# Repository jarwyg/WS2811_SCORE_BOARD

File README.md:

# WS2811_SCORE_BOARD

W 2017 wraz z znajomym z roku stworzyliśmy tablicę wyników zbudowaną z wykorzystaniem pasków LED WS2811.

W 2024 projekt został ulepszony pod względem hardware oraz firmware. Aktualnie jest opublikownay jako open-source (MIT License) 

# Firmware

Firmware jest napisany w jęzku c.
Projekt był stworzony w Eclipse z AVR plugin (kompilator avr-gcc). Katalog Release zawiera pliki makefile więc można projekt skompliować z poziomu terminala.
Gotowe pliki binarne można znaleźć poniżej

[Firmware Release v1.2](https://github.com/jarwyg/WS2811_SCORE_BOARD/releases/tag/v1.2)

# Receiver

Odbiornik działa na mikrokontrolerze Atmega88/168/328 (16MHz - zawnętrzny oscylator).
Czas jest brany z RTC PCF8563.
Płytka powinna mieć wgrany bootloader z arduino UNO. Dzięki temu po podłączeniu przejściówki USB-UART łatwiej będzie wgrać aktualizację/zobaczyć debug podczas pracy układu. Tablica prawdopodobnie będzie w niedostępnym miejscu więc zalecam zostawienie długiego przewodu USB/RS232 

PCB

# Transmitter

Pilot działa na mikrokontrolerze Atmega88/168/328 (8MHz - wewnętrzny oscylator)
Domyślnie jest w trybie uśpienia i pownien pobierać mniej niż 70uA.
Komunikacja z odbiornikiem odbywa się tylko w jedną stronę.

Opis przycisków

PCB

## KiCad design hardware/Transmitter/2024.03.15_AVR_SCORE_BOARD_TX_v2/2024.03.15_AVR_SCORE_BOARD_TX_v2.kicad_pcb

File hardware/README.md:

# WS2811_SCORE_BOARD
F_CPU 8MHz - Internal oscillator

External oscillator not required

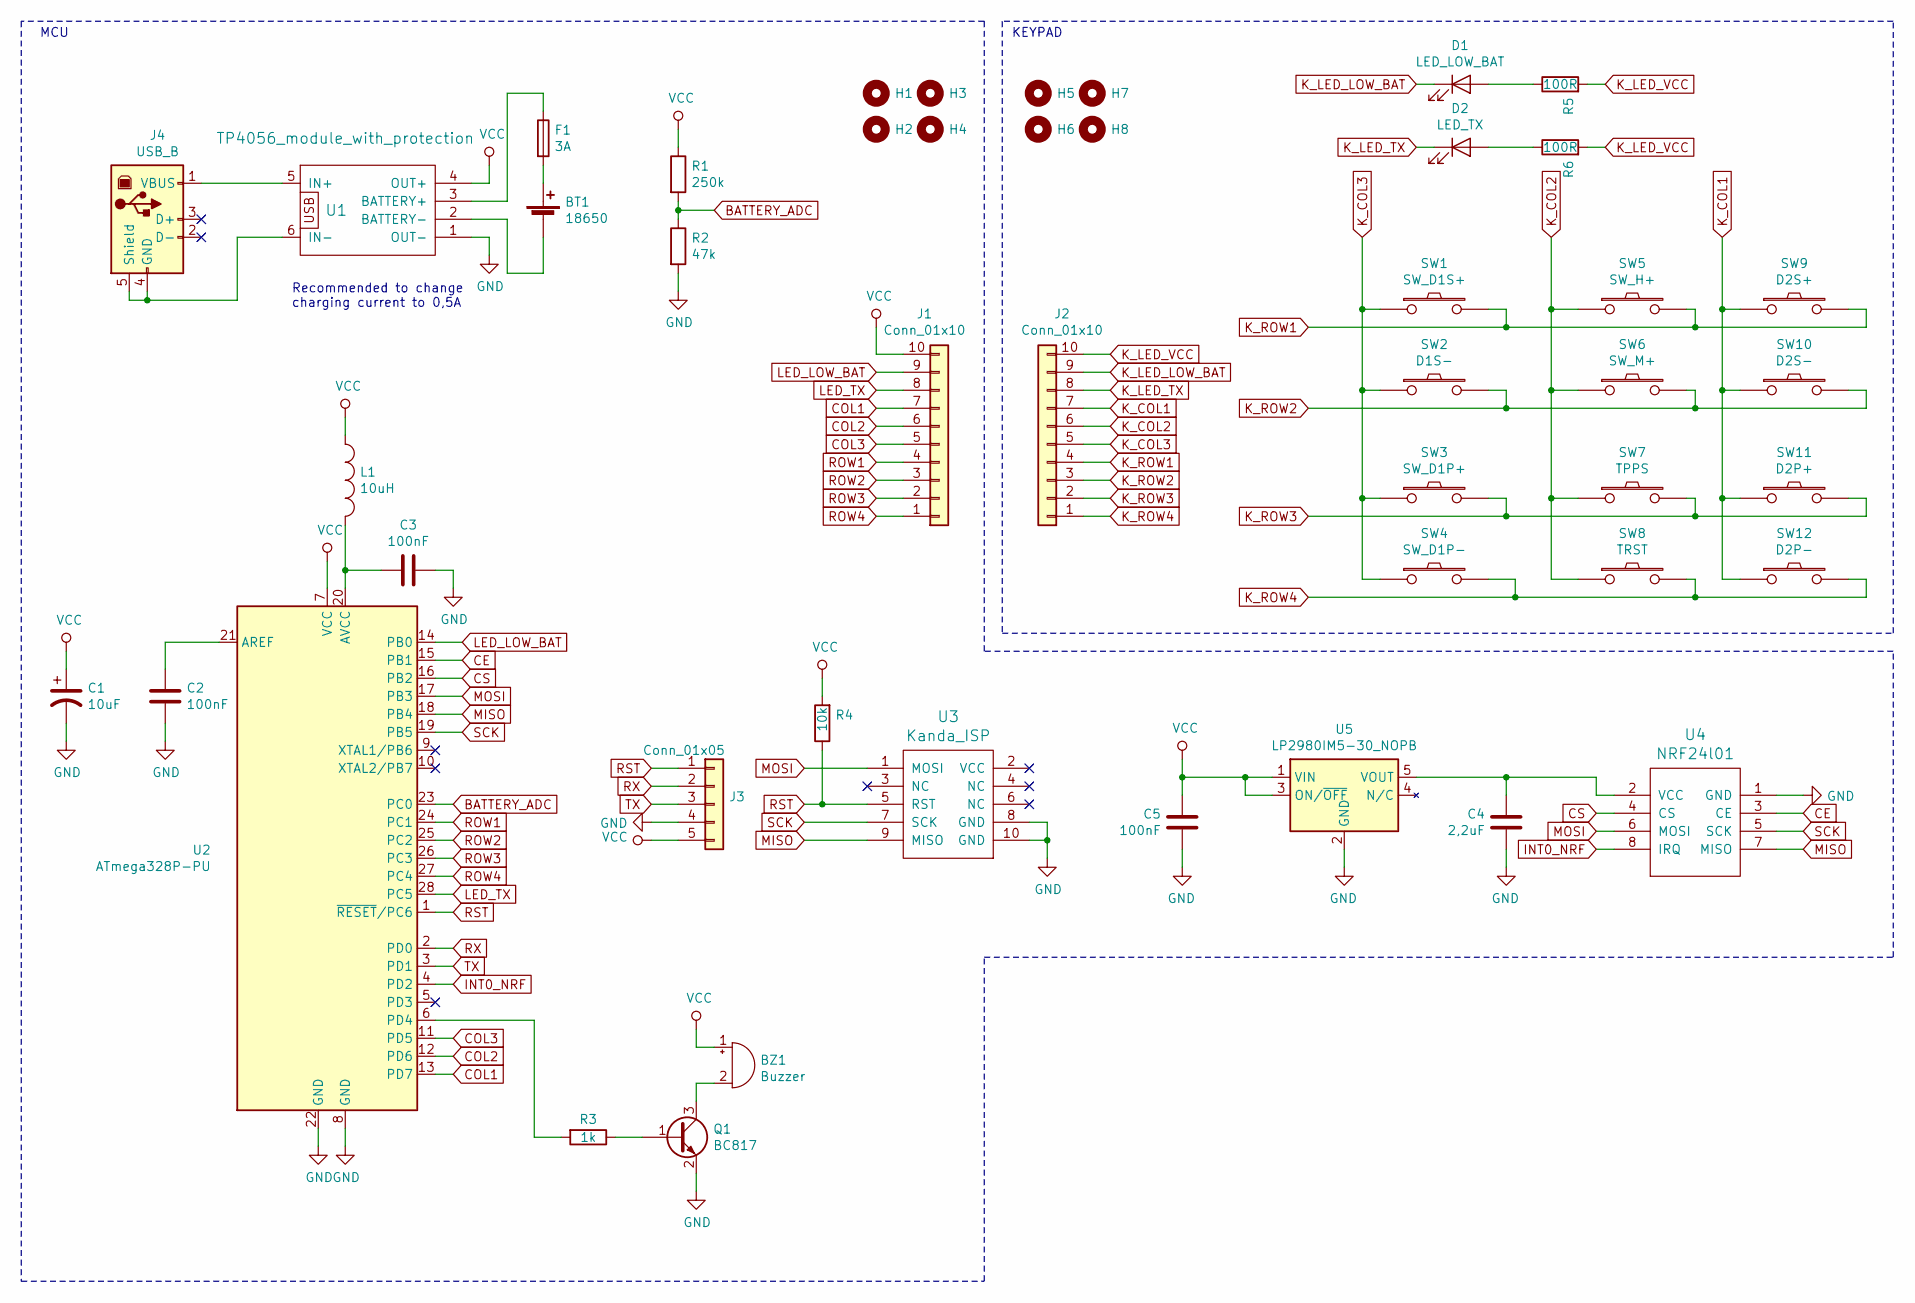
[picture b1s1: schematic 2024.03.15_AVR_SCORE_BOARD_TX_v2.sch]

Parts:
BT1: 18650; BatteryHolder_MPD_BH-18650-PC2
BZ1: Buzzer; BUZZER(7,5mm)
C1: 10uF; C(2,5mm)
C2, C3, C5: 100nF; C_0805_2012Metric_Pad1.15x1.40mm_HandSolder
C4: 2,2uF; C_0805_2012Metric_Pad1.15x1.40mm_HandSolder
D1: LED_LOW_BAT; LED_D3.0mm
D2: LED_TX; LED_D3.0mm
F1: 3A; Fuse_0805_2012Metric_Pad1.15x1.40mm_HandSolder
H1, H2, H3, H4, H5, H6, H7, H8: MountingHole; MountingHole_3mm
J1, J2: Conn_01x10; conn_10
J3: Conn_01x05; conn_5
J4: USB_B
L1: 10uH; L_0805_2012Metric_Pad1.15x1.40mm_HandSolder
Q1: BC817; SOT-23
R1: 250k; R_MY_DIN0204_L3.6mm_D1.6mm_P7.62mm
R2: 47k; R_MY_DIN0204_L3.6mm_D1.6mm_P7.62mm
R3: 1k; R_MY_DIN0204_L3.6mm_D1.6mm_P7.62mm
R4: 10k; R_0805_2012Metric_Pad1.15x1.40mm_HandSolder
R5, R6: 100R; C_0805_2012Metric_Pad1.15x1.40mm_HandSolder
SW1: SW_D1S+; SW_SMALL(12X12)
SW2: D1S-; SW_SMALL(12X12)
SW3: SW_D1P+; SW_SMALL(12X12)
SW4: SW_D1P-; SW_SMALL(12X12)
SW5: SW_H+; SW_SMALL(6X6)
SW6: SW_M+; SW_SMALL(6X6)
SW7: TPPS; SW_SMALL(12X12)
SW8: TRST; SW_SMALL(12X12)
SW9: D2S+; SW_SMALL(12X12)
SW10: D2S-; SW_SMALL(12X12)
SW11: D2P+; SW_SMALL(12X12)
SW12: D2P-; SW_SMALL(12X12)
U1: TP4056_module_with_protection; TP4056-18650
U2: ATmega328P-PU; DIP-28_W7.62mm
U3: Kanda_ISP; KANDA_ISP
U4: NRF24l01
U5: LP2980IM5-30_NOPB; SOT-23-5

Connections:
BATTERY_ADC: R1.2, R2.1, U2.23 (PC0)
CE: U2.15 (PB1), U4.3 (CE)
COL1: J1.7, U2.13 (PD7)
COL2: J1.6, U2.12 (PD6)
COL3: J1.5, U2.11 (PD5)
CS: U2.16 (PB2), U4.4 (CS)
GND: C1.2, C2.2, C3.1, C4.2, C5.2, J3.4, Q1.2 (E), R2.2, U1.1 (OUT-), U2.8 (GND), U2.22 (GND), U3.8 (GND), U3.10 (GND), U4.1 (GND), U5.2 (GND)
INT0_NRF: U2.4 (PD2), U4.8 (IRQ)
K_COL1: J2.7, SW9.1, SW10.1, SW11.1, SW12.1
K_COL2: J2.6, SW5.1, SW6.1, SW7.1, SW8.1
K_COL3: J2.5, SW1.1, SW2.1, SW3.1, SW4.1
K_LED_LOW_BAT: D1.1 (K), J2.9
K_LED_TX: D2.1 (K), J2.8
K_LED_VCC: J2.10, R5.2, R6.2
K_ROW1: J2.4, SW1.2, SW5.2, SW9.2
K_ROW2: J2.3, SW2.2, SW6.2, SW10.2
K_ROW3: J2.2, SW3.2, SW7.2, SW11.2
K_ROW4: J2.1, SW4.2, SW8.2, SW12.2
LED_LOW_BAT: J1.9, U2.14 (PB0)
LED_TX: J1.8, U2.28 (PC5)
MISO: U2.18 (PB4), U3.9 (MISO), U4.7 (MISO)
MOSI: U2.17 (PB3), U3.1 (MOSI), U4.6 (MOSI)
unnamed: BT1.1 (+), F1.2
unnamed: BT1.2 (-), U1.2 (BATTERY-)
unnamed: BZ1.2 (+), Q1.3 (C)
unnamed: C2.1, U2.21 (AREF)
unnamed: C3.2, L1.2, U2.20 (AVCC)
unnamed: C4.1, U4.2 (VCC), U5.5 (VOUT)
unnamed: D1.2 (A), R5.1
unnamed: D2.2 (A), R6.1
unnamed: F1.1, U1.3 (BATTERY+)
unnamed: J4.1 (VBUS), U1.5 (IN+)
unnamed: J4.4 (GND), J4.5 (Shield), U1.6 (IN-)
unnamed: Q1.1 (B), R3.1
unnamed: R3.2, U2.6 (PD4)
ROW1: J1.4, U2.24 (PC1)
ROW2: J1.3, U2.25 (PC2)
ROW3: J1.2, U2.26 (PC3)
ROW4: J1.1, U2.27 (PC4)
RST: J3.1, R4.1, U2.1 (~RESET~/PC6), U3.5 (RST)
RX: J3.2, U2.2 (PD0)
SCK: U2.19 (PB5), U3.7 (SCK), U4.5 (SCK)
TX: J3.3, U2.3 (PD1)
VCC: BZ1.1 (-), C1.1, C5.1, J1.10, J3.5, L1.1, R1.1, R4.2, U1.4 (OUT+), U2.7 (VCC), U5.1 (VIN), U5.3 (ON/~OFF)

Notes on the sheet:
Recommended to change charging current to 0,5A
KEYPAD
MCU

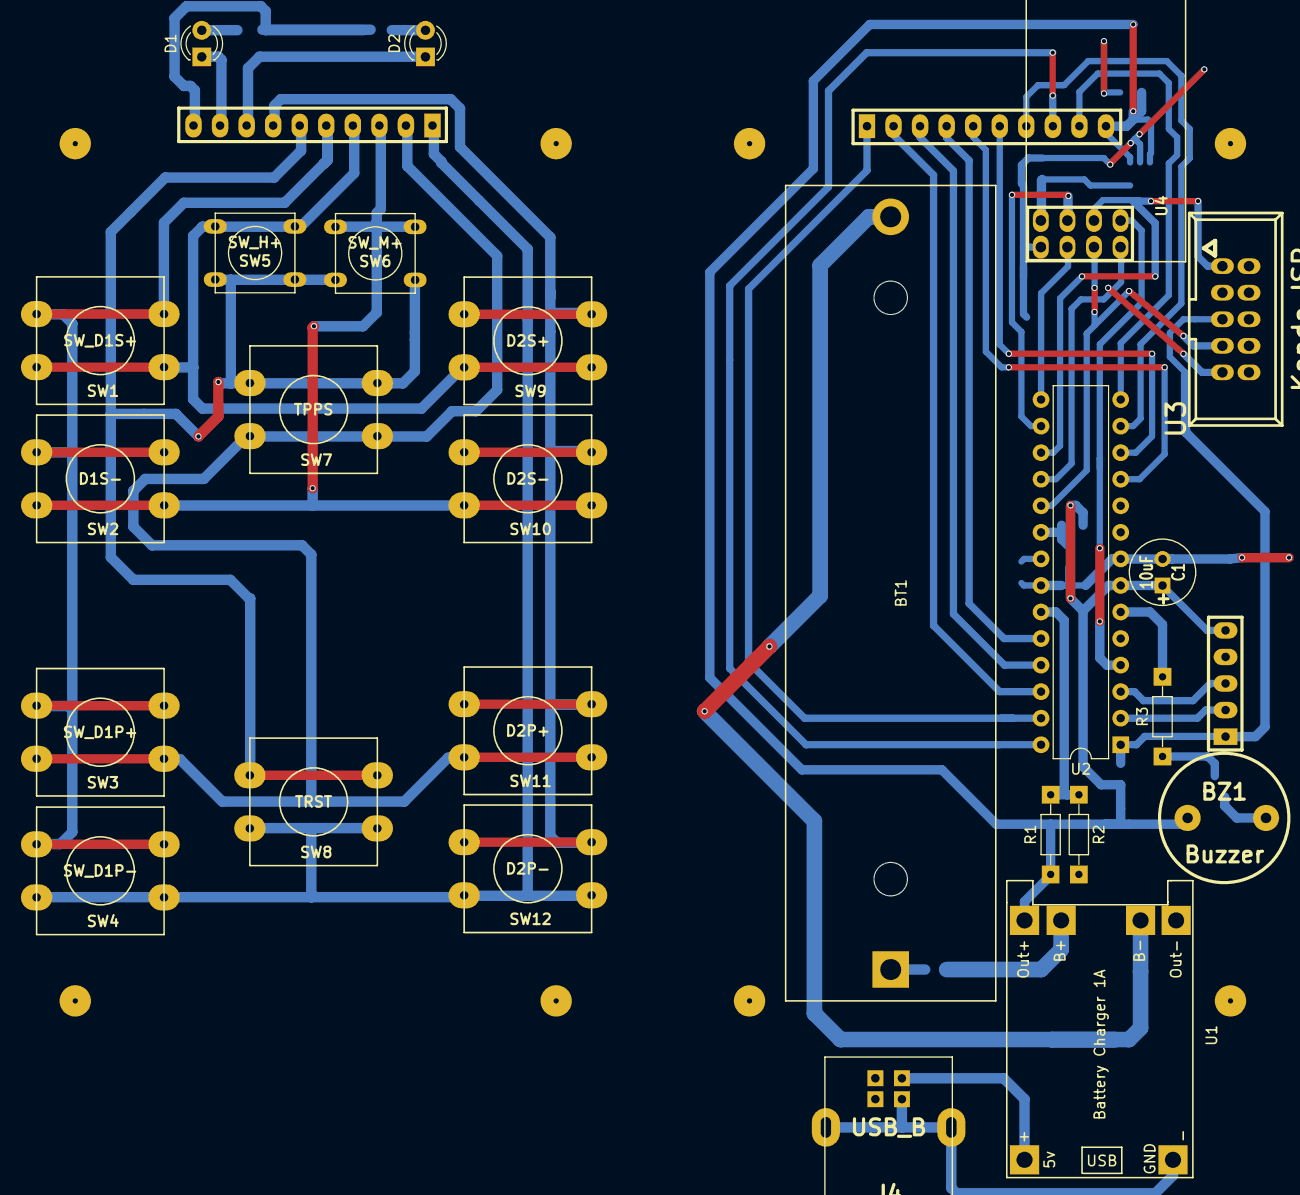
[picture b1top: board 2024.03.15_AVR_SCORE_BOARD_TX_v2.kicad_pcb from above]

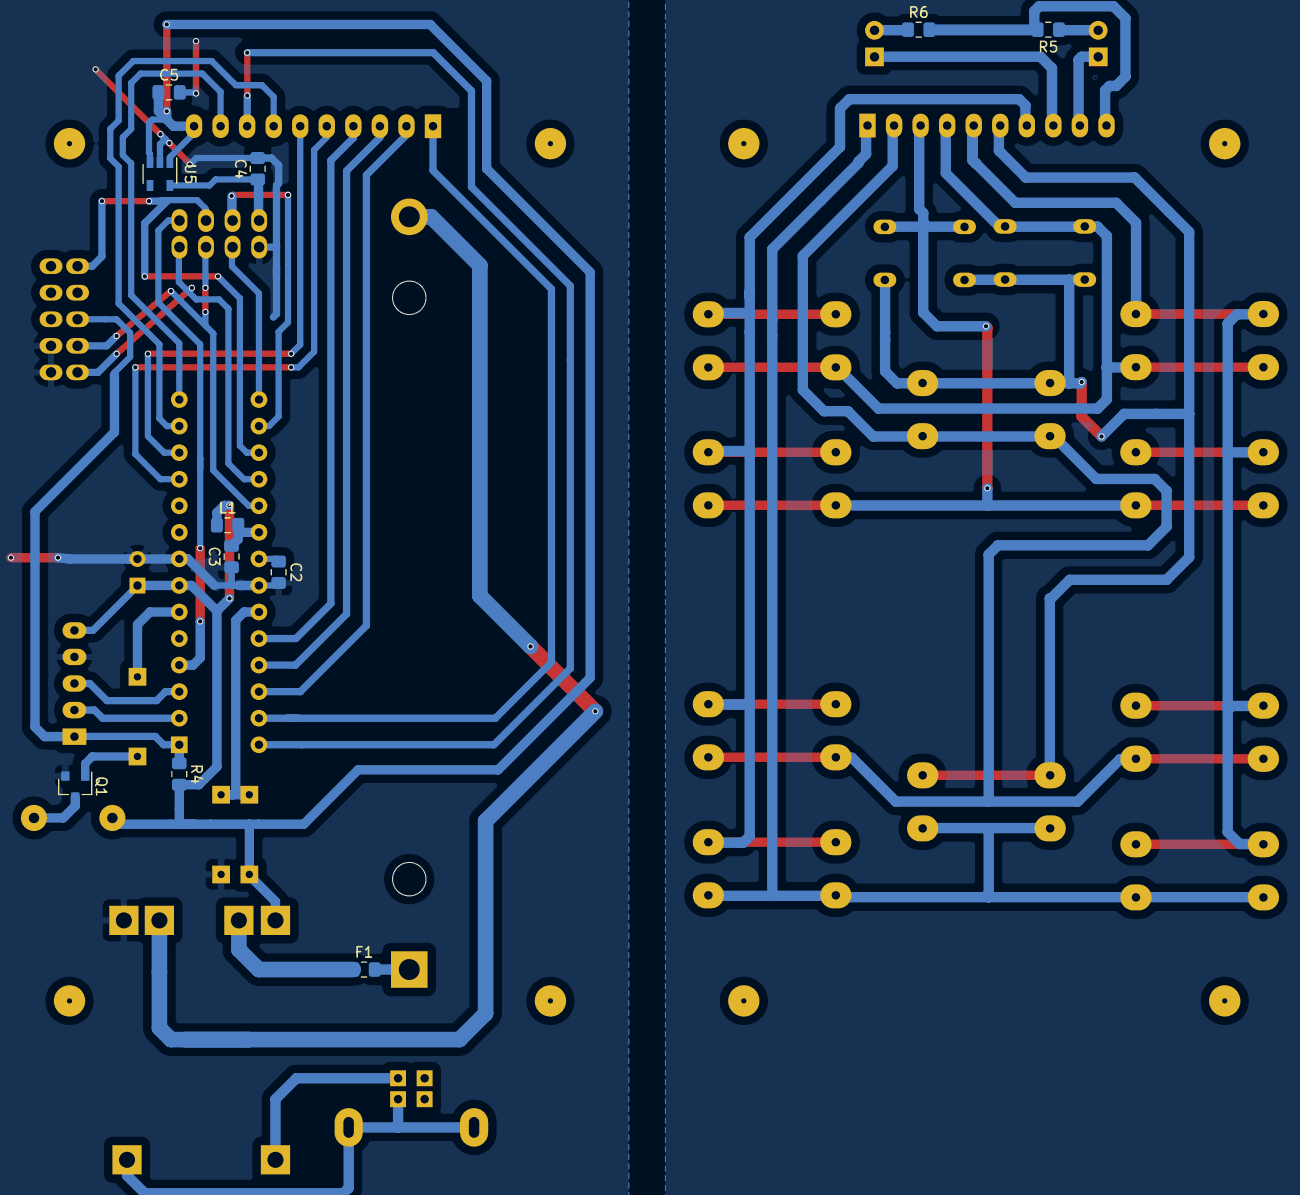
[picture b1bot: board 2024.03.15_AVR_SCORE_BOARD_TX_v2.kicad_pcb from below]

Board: 2 copper layers, 47 parts (11 on the bottom side), 44 nets.

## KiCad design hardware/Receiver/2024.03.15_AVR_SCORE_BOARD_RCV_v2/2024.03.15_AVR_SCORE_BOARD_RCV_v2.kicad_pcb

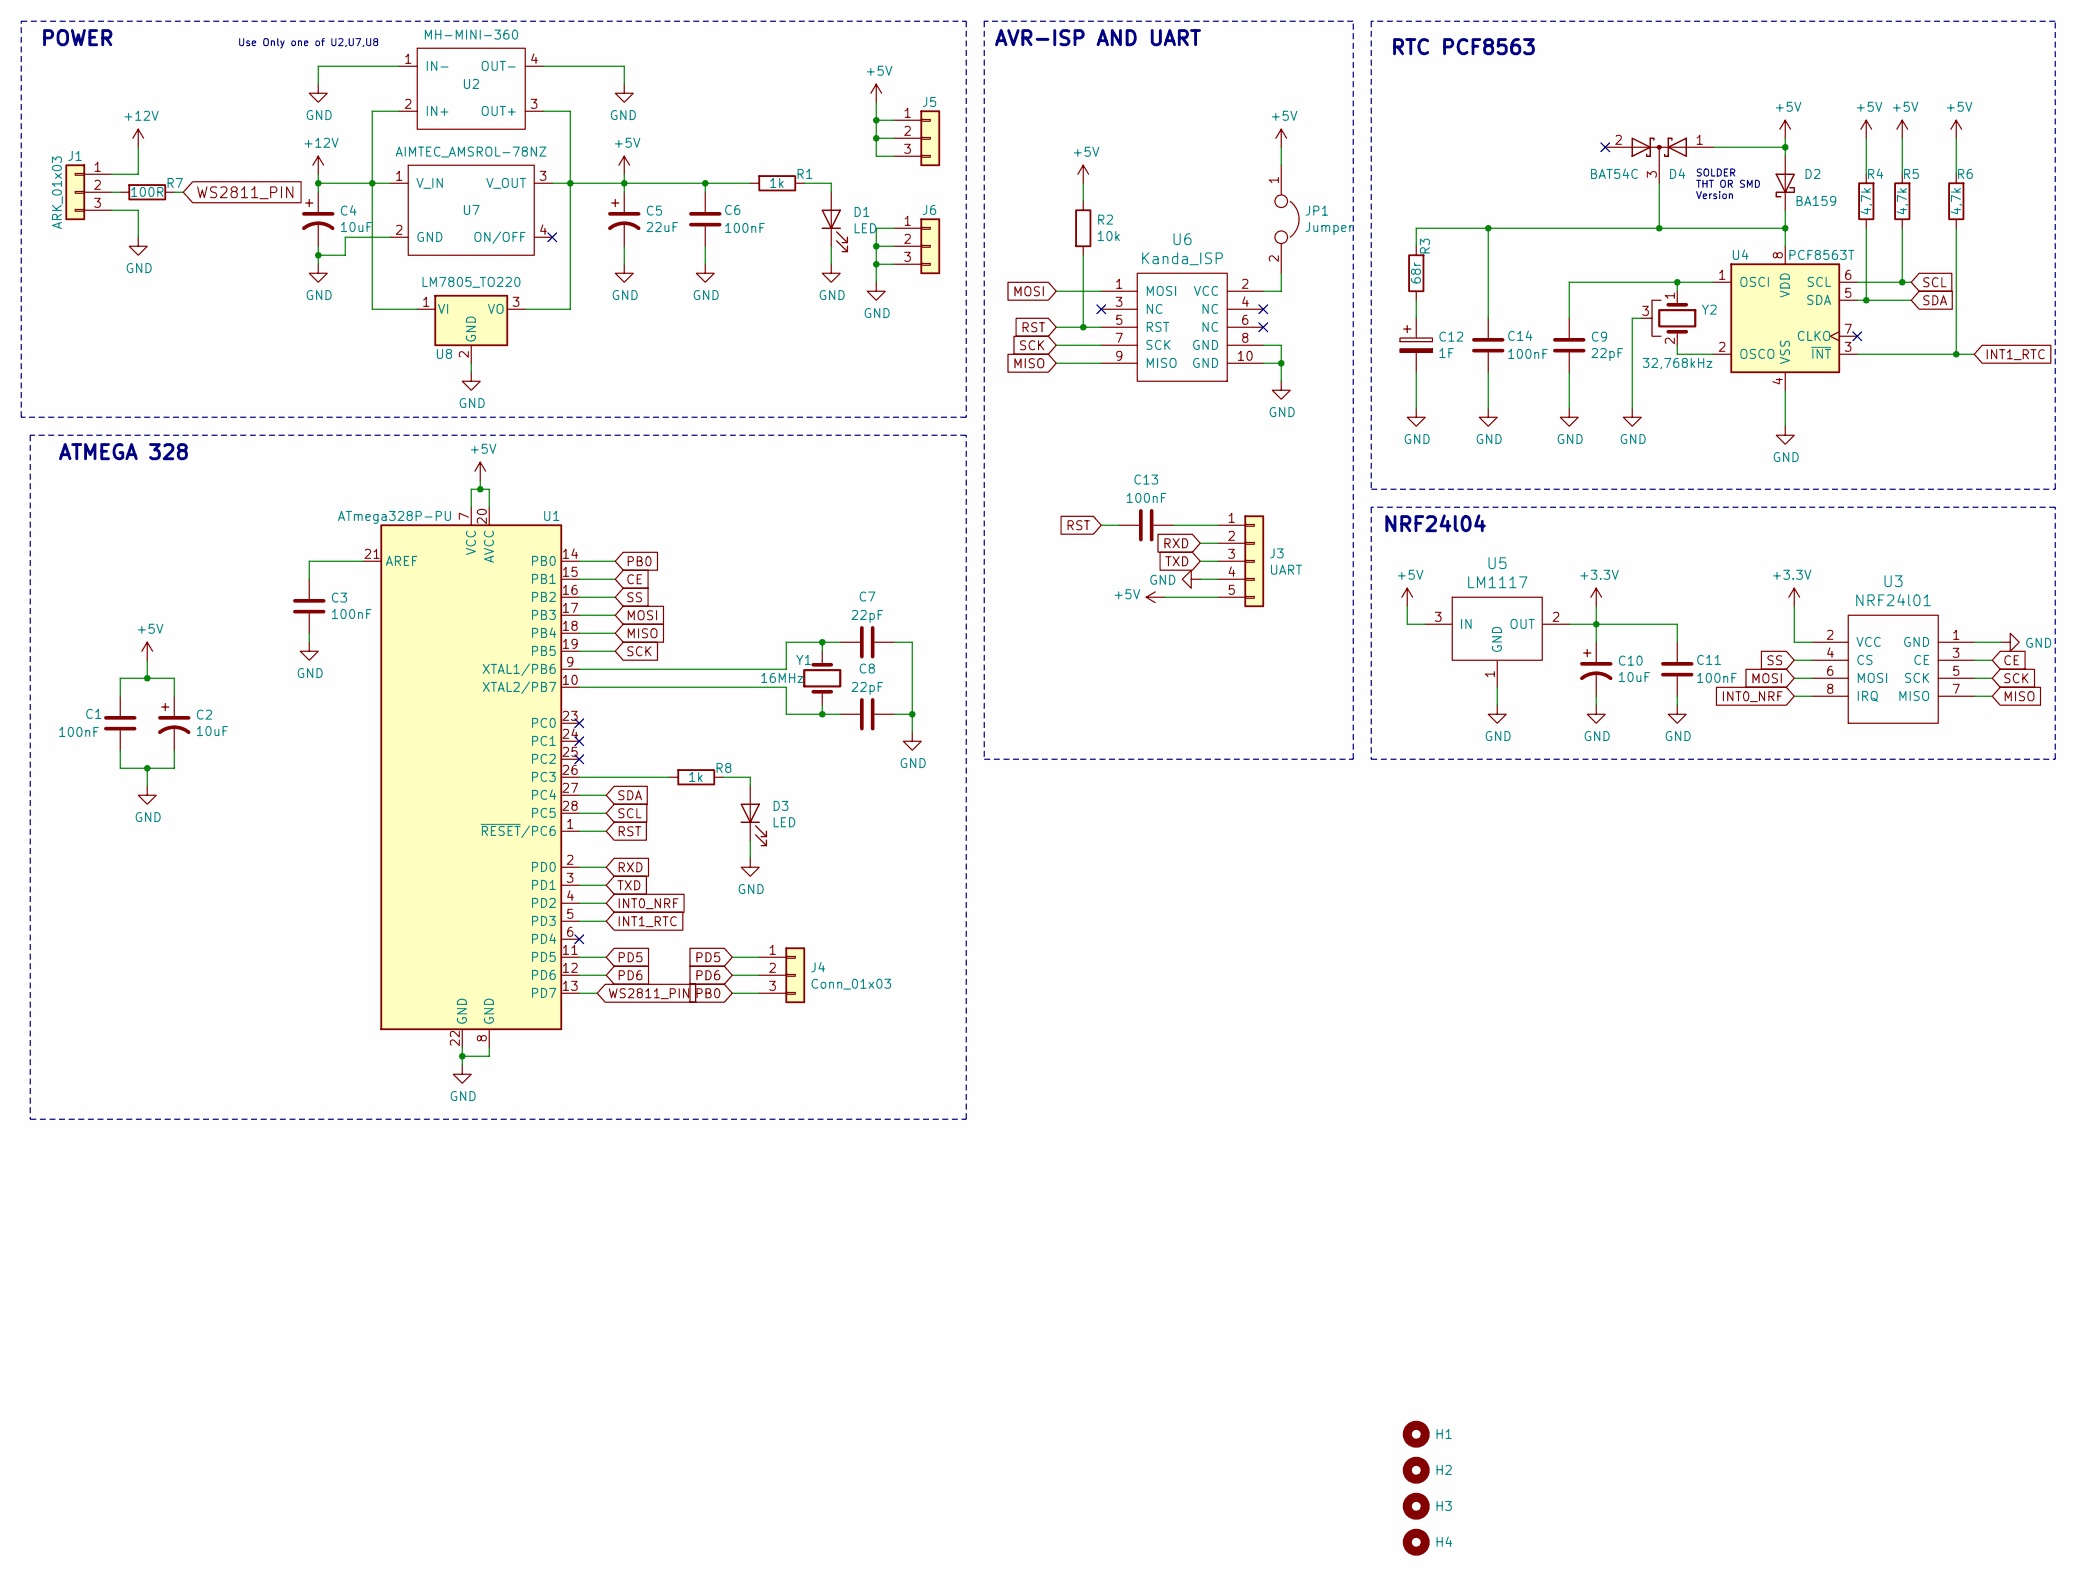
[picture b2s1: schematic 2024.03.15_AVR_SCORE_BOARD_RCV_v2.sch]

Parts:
C1, C3, C6, C11, C14: 100nF; C[5,5mm]
C2, C4, C10: 10uF; C(2,5mm)
C5: 22uF; C(2,5mm)
C7, C8, C9: 22pF; C[5,5mm]
C12: 1F; C(3,5mm)
C13: 100nF; C_0805_2012Metric_Pad1.15x1.40mm_HandSolder
D1, D3: LED; LED_D3.0mm
D2: BA159; D_A-405_P7.62mm_Horizontal
D4: BAT54C; SOT-23
H1, H2, H3, H4: MountingHole; MountingHole_3.2mm_M3
J1: ARK_01x03; ARK_3PIN
J3: UART; conn_5
J4, J5, J6: Conn_01x03; conn_3
JP1: Jumper; SolderJumper-2_P1.3mm_Open_Pad1.0x1.5mm
R1, R8: 1k; R_MY_DIN0204_L3.6mm_D1.6mm_P7.62mm
R2: 10k; R_MY_DIN0204_L3.6mm_D1.6mm_P7.62mm
R3: 68r; R_MY_DIN0204_L3.6mm_D1.6mm_P7.62mm
R4, R5, R6: 4,7k; R_MY_DIN0204_L3.6mm_D1.6mm_P7.62mm
R7: 100R; R_MY_DIN0204_L3.6mm_D1.6mm_P7.62mm
U1: ATmega328P-PU; DIP-28_W7.62mm_LongPads
U2: MH-MINI-360; MH-MINI_DC_DC
U3: NRF24l01
U4: PCF8563T; DIP-8_W7.62mm_LongPads
U5: LM1117; TO263_MY
U6: Kanda_ISP
U7: AIMTEC_AMSROL-78NZ; AMSROL-78NZ
U8: LM7805_TO220; TO-220-3_Vertical
Y1: 16MHz; Crystal_HC49-U_Vertical
Y2: 32,768kHz; Crystal_DS10_D1.0mm_L4.3mm_Horizontal_1EP_style2

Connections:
+3V3: C10.1, C11.1, U3.2 (VCC), U5.2 (OUT)
+5V: C1.1, C2.1, C5.1, C6.1, D2.2 (A), D4.1 (A), J3.5, J5.1, J5.2, J5.3, JP1.1, R1.2, R2.1, R4.2, R5.2, R6.2, U1.7 (VCC), U1.20 (AVCC), U2.3 (OUT+), U5.3 (IN), U7.3 (V_OUT), U8.3 (VO)
+12V: C4.1, J1.1, U2.2 (IN+), U7.1 (V_IN), U8.1 (VI)
CE: U1.15 (PB1), U3.3 (CE)
GND: C1.2, C2.2, C3.2, C4.2, C5.2, C6.2, C7.1, C8.1, C9.2, C10.2, C11.2, C12.2, C14.2, D1.1 (K), D3.1 (K), J1.3, J3.4, J6.1, J6.2, J6.3, U1.8 (GND), U1.22 (GND), U2.1 (IN-), U2.4 (OUT-), U3.1 (GND), U4.4 (VSS), U5.1 (GND), U6.8 (GND), U6.10 (GND), U7.2 (GND), U8.2 (GND), Y2.3
INT0_NRF: U1.4 (PD2), U3.8 (IRQ)
INT1_RTC: R6.1, U1.5 (PD3), U4.3 (~INT~)
MISO: U1.18 (PB4), U3.7 (MISO), U6.9 (MISO)
MOSI: U1.17 (PB3), U3.6 (MOSI), U6.1 (MOSI)
unnamed: C3.1, U1.21 (AREF)
unnamed: C7.2, U1.9 (XTAL1/PB6), Y1.2
unnamed: C8.2, U1.10 (XTAL2/PB7), Y1.1
unnamed: C9.1, U4.1 (OSCI), Y2.1
unnamed: C12.1, R3.1
unnamed: C13.1, J3.1
unnamed: C14.1, D2.1 (K), D4.3 (K), R3.2, U4.8 (VDD)
unnamed: D1.2 (A), R1.1
unnamed: D3.2 (A), R8.1
unnamed: J1.2, R7.2
unnamed: JP1.2, U6.2 (VCC)
unnamed: R8.2, U1.26 (PC3)
unnamed: U4.2 (OSCO), Y2.2
PB0: J4.3, U1.14 (PB0)
PD5: J4.1, U1.11 (PD5)
PD6: J4.2, U1.12 (PD6)
RST: C13.2, R2.2, U1.1 (~RESET~/PC6), U6.5 (RST)
RXD: J3.2, U1.2 (PD0)
SCK: U1.19 (PB5), U3.5 (SCK), U6.7 (SCK)
SCL: R5.1, U1.28 (PC5), U4.6 (SCL)
SDA: R4.1, U1.27 (PC4), U4.5 (SDA)
SS: U1.16 (PB2), U3.4 (CS)
TXD: J3.3, U1.3 (PD1)
WS2811_PIN: R7.1, U1.13 (PD7)

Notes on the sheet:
AVR-ISP AND UART
POWER
RTC PCF8563
NRF24l04
ATMEGA 328
SOLDER THT OR SMD Version
Use Only one of U2,U7,U8

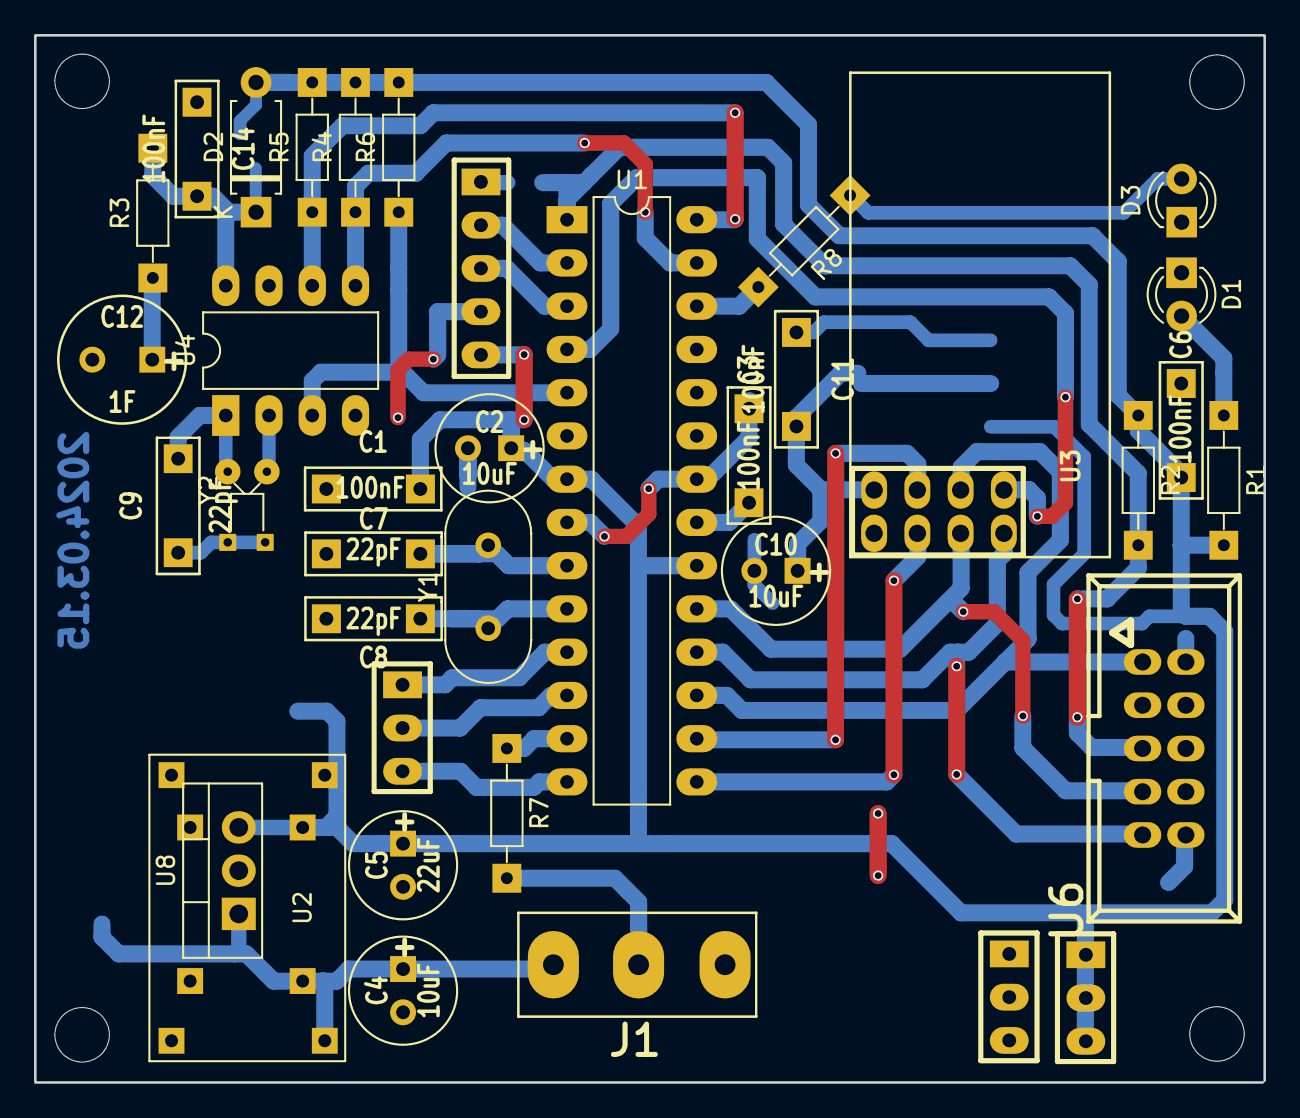
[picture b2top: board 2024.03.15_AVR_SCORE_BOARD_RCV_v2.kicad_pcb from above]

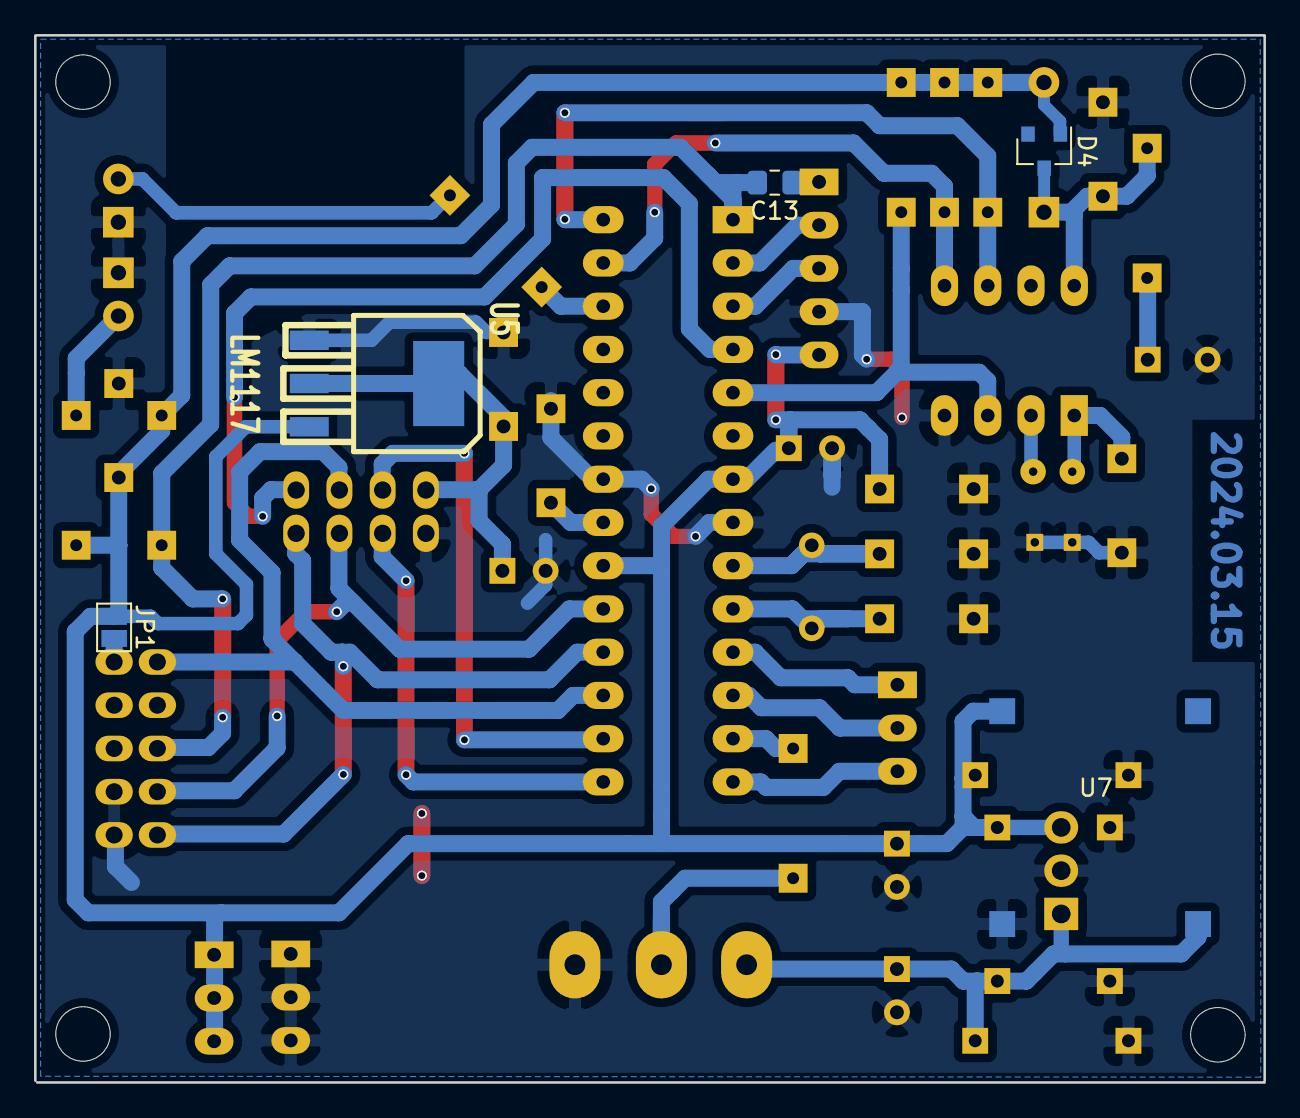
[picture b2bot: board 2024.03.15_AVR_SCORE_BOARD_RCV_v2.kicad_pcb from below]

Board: 2 copper layers, 72.2 x 61.5 mm, 46 parts (5 on the bottom side), 33 nets.

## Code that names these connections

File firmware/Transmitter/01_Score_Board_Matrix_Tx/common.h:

/*
 * common.h
 *
 *  Created on: Sep 10, 2018
 *      Author: user
 */

#ifndef COMMON_H_
#define COMMON_H_

//#define DBG


#define K_DELAY_TIME 200


#define BUZZ (1<<PD7)
#define BUZZ_ON PORTD |= BUZZ
#define BUZZ_OFF PORTD &= ~BUZZ

#define LED_R_LOW_BATT (1<<PB0)
#define LED_R_LOW_BATT_PIN_SET_AS_OUT DDRB |= LED_R_LOW_BATT
#define LED_R_LOW_BATT_ON PORTB &= ~LED_R_LOW_BATT
#define LED_R_LOW_BATT_OFF PORTB |= LED_R_LOW_BATT

#define LED_G_TX (1<<PC5)
#define LED_G_TX_PIN_SET_AS_OUT DDRC |= LED_G_TX
#define LED_G_TX_ON PORTC &= ~LED_G_TX
#define LED_G_TX_OFF PORTC |= LED_G_TX


#define COL_DDR DDRD
#define COL_PORT PORTD
#define COL_PIN PIND

#define COL1_PIN (1<<7)
#define COL2_PIN (1<<6)
#define COL3_PIN (1<<5)

#define ROW_DDR DDRC
#define ROW_PORT PORTC
#define ROW_PIN PINC

#define ROW1_PIN (1<<1)
#define ROW2_PIN (1<<2)
#define ROW3_PIN (1<<3)
#define ROW4_PIN (1<<4)

#define COLUMN_gm   (COL1_PIN|COL2_PIN|COL3_PIN)
#define ROWS_gm   (ROW1_PIN|ROW2_PIN|ROW3_PIN|ROW4_PIN)



volatile uint8_t timer_0, timer_1,timer_2;
uint8_t timer_1_lock, timer_2_lock;

void parse_uart_data( char * pBuf );

void beep(void);
void CheckBattery(void);

void SendStr(uint8_t *charr);

void CheckKeys(uint8_t key_pressed);
void go_to_sleep(void);

#endif /* COMMON_H_ */

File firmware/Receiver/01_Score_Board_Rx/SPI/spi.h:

/*
	spi lib 0x01

	copyright (c) Davide Gironi, 2012

	References:
	  -  This library is based upon SPI avr lib by Stefan Engelke
		 http://www.tinkerer.eu/AVRLib/SPI

	Released under GPLv3.
	Please refer to LICENSE file for licensing information.
*/


#ifndef _SPI_H_
#define _SPI_H_

#include <avr/io.h>

//spi ports
#define SPI_DDR DDRB
#define SPI_PORT PORTB
#define SPI_MISO PB4
#define SPI_MOSI PB3
#define SPI_SCK PB5
#define SPI_SS PB2

//NRF24l01 CE PB1
//NRF24l01 CSN PB2

extern void spi_init();
extern uint8_t spi_writereadbyte(uint8_t data);

#endif

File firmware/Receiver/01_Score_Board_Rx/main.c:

/*
 * main.c
 *
 *  Created on: Mar 17, 2018
 *      Author: user
 */

#include <stdio.h>
#include <stdlib.h>
#include <string.h>
#include <avr/io.h>
#include <avr/interrupt.h>

#include <avr/pgmspace.h>
#include <util/delay.h>

#include "nrf24l01/nrf24l01.h"


#include "Light_WS2812/light_ws2812.h"
#include "Light_WS2812/led_led.h"


#include "I2C_TWI/pcf8563p.h"
#include "I2C_TWI/i2c.h"

#include "UART/uart.h"


volatile uint8_t int1_flag = 0;


void disp_time(void){

	rtc_refresh_date();

	dwukropek =! dwukropek;

	update_LED();
}




int main(void) {

	_delay_ms(1000);//wait to init pcf8563

	DDRC |= (1<<PC3);//

//	PORTC |= (1<<PC4) | (1<<PC5);//pullup on SDA and SCL - for arduino

	DDRD |= (1<<ws2812_pin);

	char bufferin[NRF24L01_PAYLOAD];


	//enable RTC interrupt (INT1)
	EICRA |= (1 << ISC11);
	EIMSK |= (1 << INT1);
//	PORTD |= (1 << PD3); //not needed if hardware pullup resistor is placed

	uart_init(UBRR);
	uart_puts("Score Board v2.0\r\n");

	nrf24l01_init();

	sei();

	i2cSetBitrate(100);

	rtc_init();

	off_timer = SECONDS_TO_SUSPEND;

	update_LED();

	while (1) {


		if(int1_flag){


			PORTC ^= (1<<PC3);


			if(play_time_on == 1){
				play_time_ss++;
				if(play_time_ss == 60){
					play_time_mm++;
					play_time_ss = 0;
				}
				if(play_time_mm == 60) play_time_mm = 0;
			}


			if(off_timer != 0){
				off_timer--; //decrementing time to disable leds
			}
			disp_time();

			uart_putlong(pcf8563_rtc.hours, 10);
			uart_putc(':');
			uart_putlong(pcf8563_rtc.minutes, 10);
			uart_putc(':');
			uart_putlong(pcf8563_rtc.seconds, 10);
			
			
			uart_puts(" off_timer: ");
			uart_putlong(off_timer, 10);
			uart_putc('\r');
			uart_putc('\n');
			

			int1_flag = 0;
		}


		uint8_t pipe = 0;
		if (nrf24l01_readready(&pipe)) { //if data is ready
			off_timer = SECONDS_TO_SUSPEND;


			//read buffer
			nrf24l01_read((uint8_t*)bufferin);

			if(!strcmp(bufferin, "D1S+")){//setyA++
				set_A++;
			}
			else if(!strcmp(bufferin, "D1S-")){//setyA--
				set_A--;
			}
			else if(!strcmp(bufferin, "D1P+")){//punktyA++
				punkty_A++;
			}
			else if(!strcmp(bufferin, "D1P-")){//punktyA--
				punkty_A--;
			}
			else if(!strcmp(bufferin, "D2S+")){//setyB++
				set_B++;
			}
			else if(!strcmp(bufferin, "D2S-")){//setyB--
				set_B--;
			}
			else if(!strcmp(bufferin, "D2P+")){//punktyB++
				punkty_B++;
			}
			else if(!strcmp(bufferin, "D2P-")){//punktyB--
				punkty_B--;
			}
			else if(!strcmp(bufferin, "RSTS")){//sety rst
				set_A=0;
				set_B=0;
			}
			else if(!strcmp(bufferin, "RSTP")){//punkty rst
				punkty_A=0;
				punkty_B=0;
			}
			else if(!strcmp(bufferin, "TPPS")){//play time on off
				play_time_on ^= 1;
			}
			else if(!strcmp(bufferin, "TRST")){//play time rst
				play_time_mm = 0;
				play_time_ss = 0;
			}
			else if(!strcmp(bufferin, "HOR+")){//hours
				pcf8563_rtc.hours++;
				if(pcf8563_rtc.hours >= 24)pcf8563_rtc.hours = 0;
				rtc_write_date();
				disp_time();

			}
			else if(!strcmp(bufferin, "MIN+")){//minutes
				pcf8563_rtc.minutes++;
				if(pcf8563_rtc.minutes >= 60)pcf8563_rtc.minutes = 0;
				rtc_write_date();
				disp_time();
			}

			uart_puts("rx cmd: ");
			uart_puts(bufferin);
			uart_putc('\r');
			uart_putc('\n');

			update_LED();


		}


	}//end WHILE
}//end MAIN



ISR( INT1_vect ) {
	int1_flag = 1;
}

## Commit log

2024-02-21 schematics
2024-02-21 add readme
2024-03-02 move LICENSE
2024-03-10 RX Board Firmware
2024-03-12 LEDs Wiring
2024-03-15 Hardware v2
2024-03-23 change design to 5v logic level
2024-03-23 changed wrong footprints
2024-04-04 Added 100nF capacitor for rtc
2024-04-19 Added v2 version of TX schematic and pcb
2024-04-20 Added LP2980 voltage regulator for NRF24L01
2024-04-20 Fixed NRF24L01 schematic symbol
2024-06-06 RCV Hardware updated - Voltage regulation
2024-06-06 Added TX firmware source files
2024-10-24 Added USB_B for charging and moved old schematic
2024-10-24 Add RCV schematic in PDF
2024-11-22 Updated gitignore
2024-12-05 Added debug and changed nrf speed
2024-12-17 Added AVR Sleep
2024-12-17 Added Release folder
2024-12-17 UART debug messages
2025-01-13 Added ADC check
2025-03-06 Ground fill fixed
2025-04-07 ADC Average
2025-05-19 NRF lib fix
2025-05-19 Update label
